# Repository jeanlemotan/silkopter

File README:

#########################################################################
#                                                                       #
#                                                                       #
#                                                                       #
#    _____ _ _ _           _                                            #
#   |   __|_| | |_ ___ ___| |_ ___ ___                                  #
#   |__   | | | '_| . | . |  _| -_|  _|                                 #
#   |_____|_|_|_,_|___|  _|_| |___|_|                                   #
#                     |_|                                               #
#                                                                       #
#                                                                       #
#  Copyright (C) 2014 Catalin Vasile                                    #
#                                                                       #
#  Web:     http://jeanleflambeur.wordpress.com/                        #
#  e-mail:  catalin.vasile@gmail.com                                    #
#                                                                       #
#                                                                       #
#########################################################################

This contains the code for the Silkopter UAV controller, ground station, simulator and additional libraries.

Folders:

qbase - base library with various utilities
qdata - filesystem and stream library
qinput - gamepad, mouse, touch and keyboard abstraction
qmath - math lib
q - 3d rendering engine used by the simulator and ground station
silkopter/fc - flight controller
silkopter/gs - ground station
silkopter/rc - remote control
silkopter/libs - common code used by the brain, gs and sim projects
printing/gimbal - a raspberry pi camera 2 axis gimbal
electrical/fc - eagle schematic and board layout for the silkopter fc

The q* libraries started initially as a mobile 3d game engine so most of the code is very game-oriented.

There are QTCreator projects in each folder and the whole code heavily uses C++11. It should compile with GCC4.7+ and clang3.2+

For licensing, check the LICENSE.txt file.

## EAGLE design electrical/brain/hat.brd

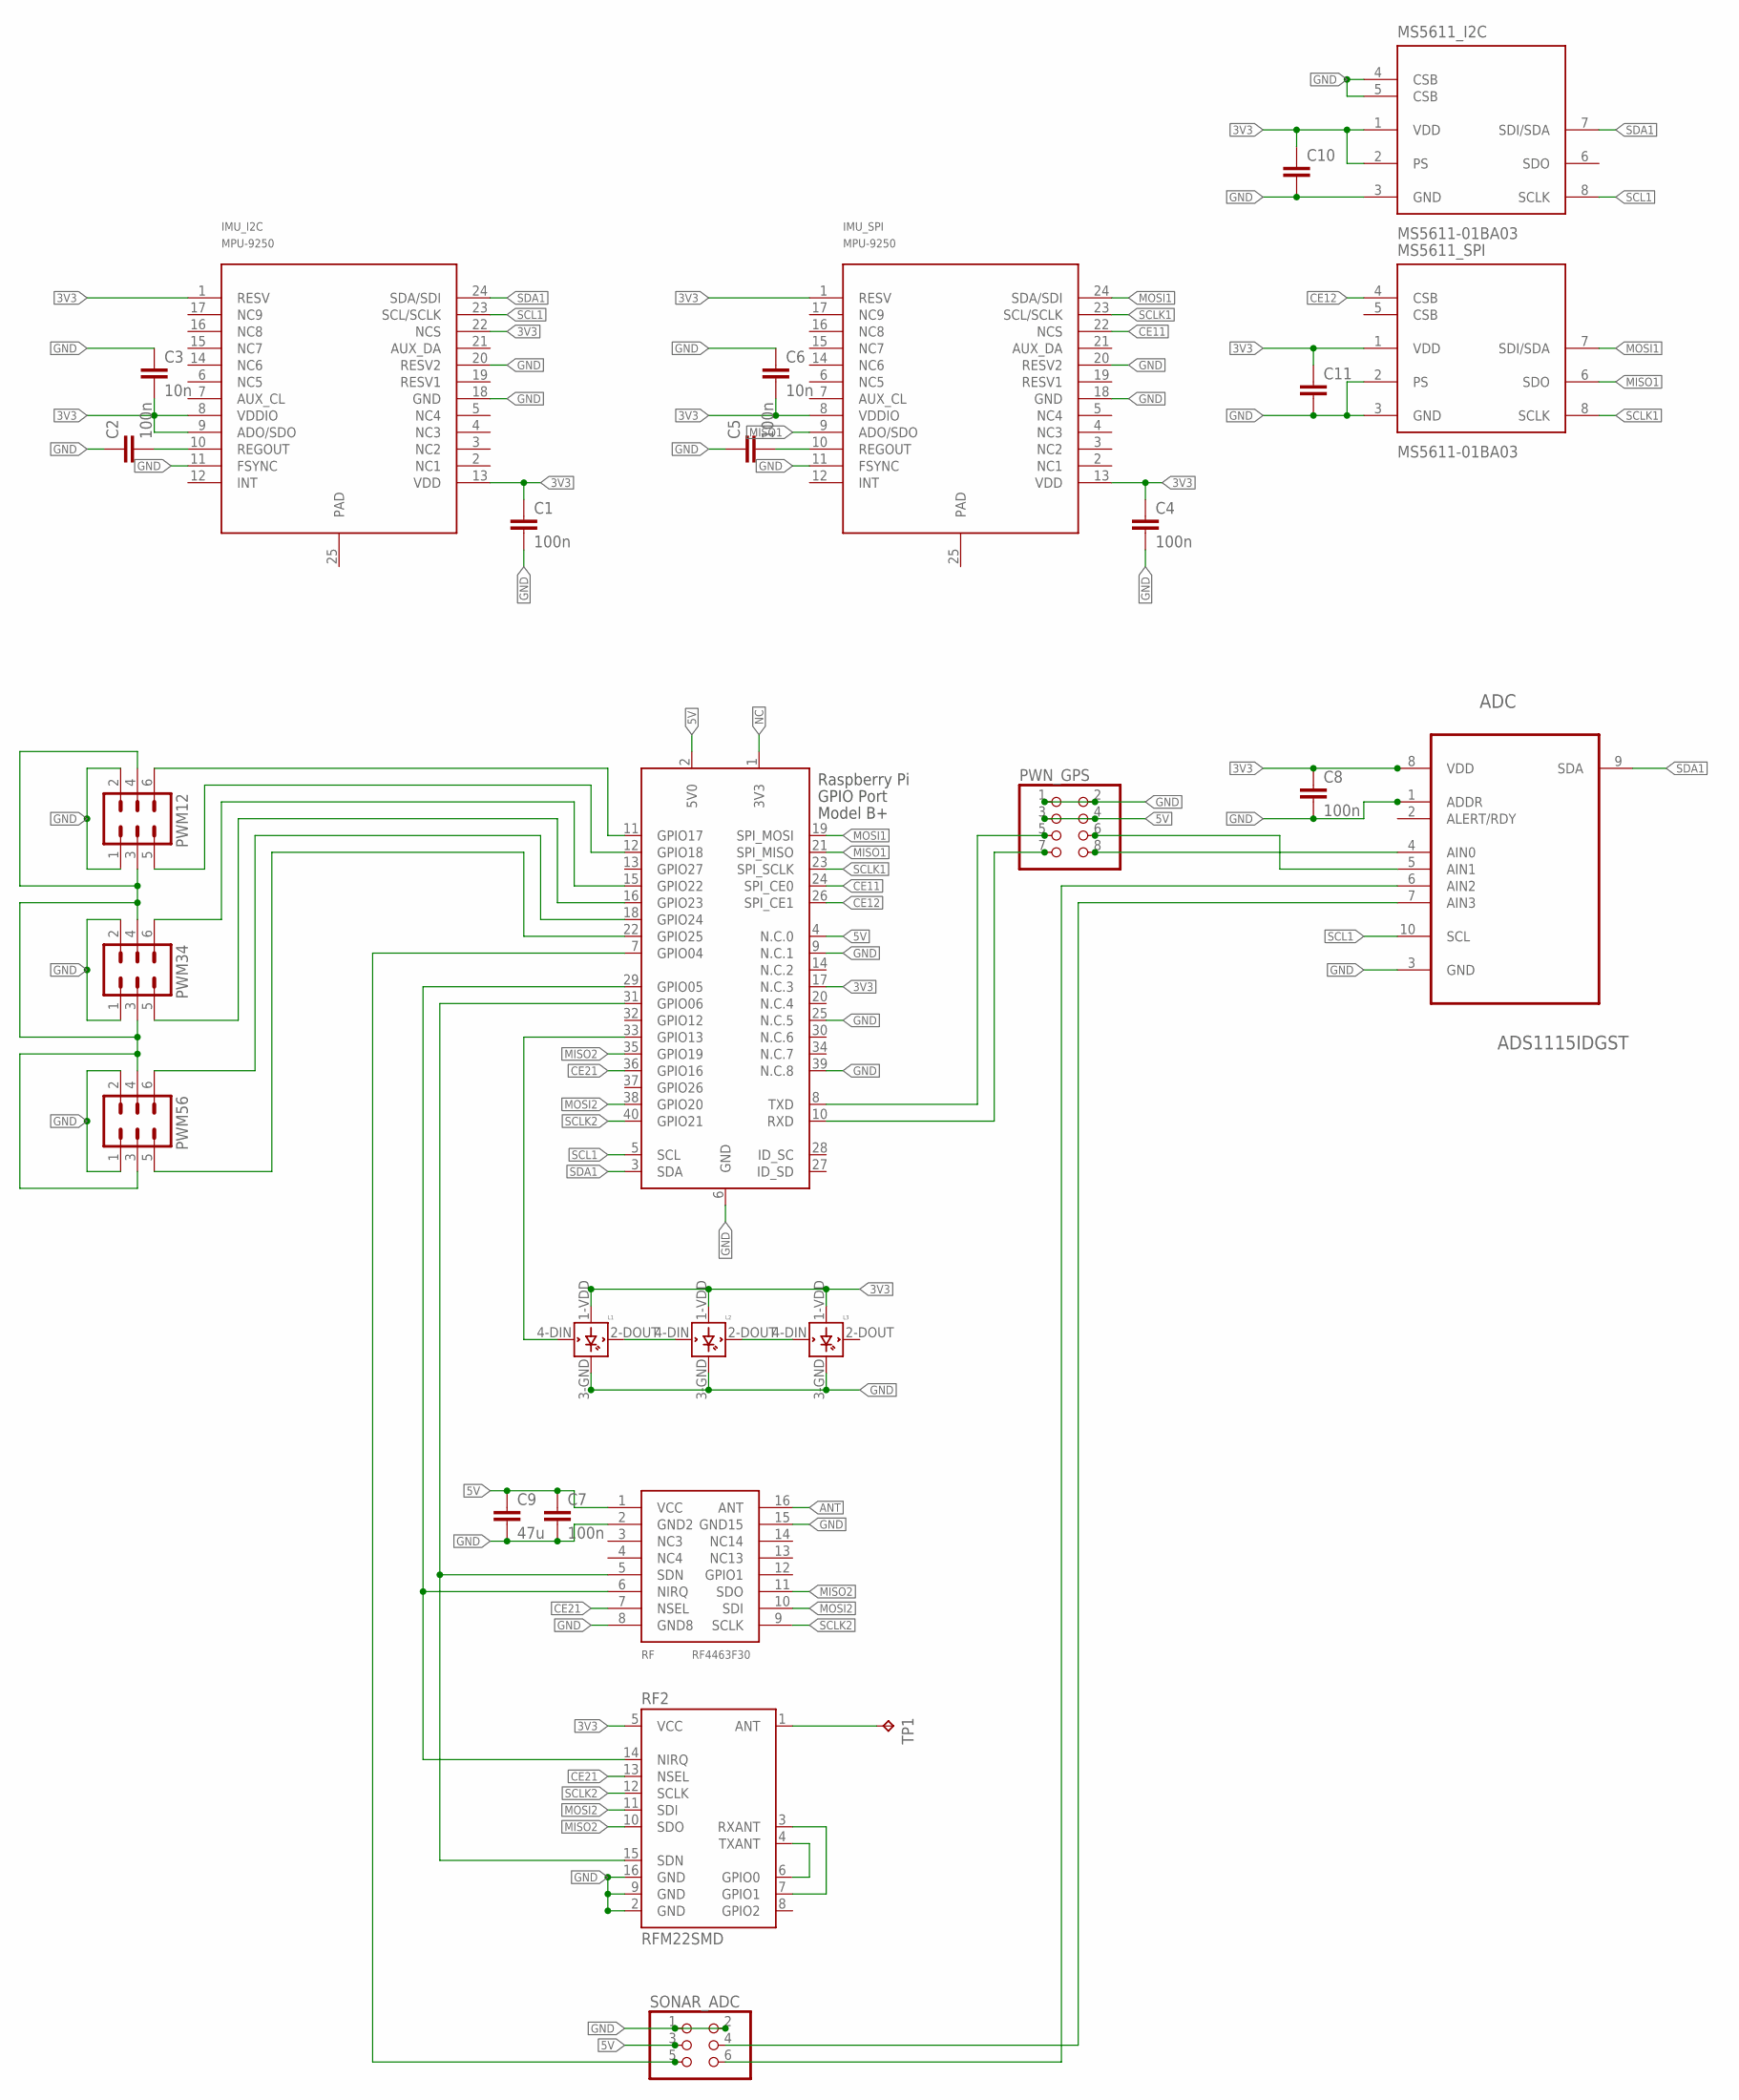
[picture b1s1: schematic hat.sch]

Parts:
ADC: ADS1115IDGST; SOP50P490X110-10N
C1, C2, C4, C5, C7, C8: 100n; C0603
C3, C6: 10n; C0603
C9: 47u; C0603
C10, C11: C-EUC0603; C0603
IMU_I2C: MPU-9250; LEAD-QFN24
IMU_SPI: MPU-9250; LEAD-QFN24
L1, L2, L3: WS2812B
MS5611_I2C, MS5611_SPI: MS5611-01BA03; SON125P300X500X100-8N
PWM12, PWM34, PWM56: MA03-2
PWN_GPS: PINHD-2X4/90; 2X04/90
RF: RF4463F30
RF2: RFM22SMD; RFM22-XXX-S2
SONAR_ADC: PINHD-2X3/90; 2X03/90
TP1: TPTP20SQ; TP20SQ
X1: RASPI_BOARD_B+_H; RASPI_BOARD_B+HAT

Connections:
3V3: ADC.8 (VDD), C1.1, C3.2, C4.1, C6.2, C8.1, C10.1, C11.1, IMU_I2C.1 (RESV), IMU_I2C.8 (VDDIO), IMU_I2C.9 (ADO/SDO), IMU_I2C.13 (VDD), IMU_I2C.22 (NCS), IMU_SPI.1 (RESV), IMU_SPI.8 (VDDIO), IMU_SPI.13 (VDD), L1.1-VDD (VDD), L2.1-VDD (VDD), L3.1-VDD (VDD), MS5611_I2C.1 (VDD), MS5611_I2C.2 (PS), MS5611_SPI.1 (VDD), RF2.5 (VCC), X1.17 (N.C.3)
5V: C7.1, C9.1, PWN_GPS.3, PWN_GPS.4, RF.1 (VCC), SONAR_ADC.3, X1.2 (5V0), X1.4 (N.C.0)
ANT: RF.16 (ANT)
CE11: IMU_SPI.22 (NCS), X1.24 (SPI_CE0)
CE12: MS5611_SPI.4 (CSB), X1.26 (SPI_CE1)
CE21: RF.7 (NSEL), RF2.13 (NSEL), X1.36 (GPIO16)
GND: ADC.1 (ADDR), ADC.3 (GND), C1.2, C2.1, C3.1, C4.2, C5.1, C6.1, C7.2, C8.2, C9.2, C10.2, C11.2, IMU_I2C.11 (FSYNC), IMU_I2C.18 (GND), IMU_I2C.20 (RESV2), IMU_SPI.11 (FSYNC), IMU_SPI.18 (GND), IMU_SPI.20 (RESV2), L1.3-GND (GND), L2.3-GND (GND), L3.3-GND (GND), MS5611_I2C.3 (GND), MS5611_I2C.4 (CSB), MS5611_I2C.5 (CSB), MS5611_SPI.2 (PS), MS5611_SPI.3 (GND), PWM12.1, PWM12.2, PWM34.1, PWM34.2, PWM56.1, PWM56.2, PWN_GPS.1, PWN_GPS.2, RF.2 (GND2), RF.8 (GND8), RF.15 (GND15), RF2.2 (GND), RF2.9 (GND), RF2.16 (GND), SONAR_ADC.1, SONAR_ADC.2, X1.6 (GND), X1.9 (N.C.1), X1.25 (N.C.5), X1.39 (N.C.8)
MISO1: IMU_SPI.9 (ADO/SDO), MS5611_SPI.6 (SDO), X1.21 (SPI_MISO)
MISO2: RF.11 (SDO), RF2.10 (SDO), X1.35 (GPIO19)
MOSI1: IMU_SPI.24 (SDA/SDI), MS5611_SPI.7 (SDI/SDA), X1.19 (SPI_MOSI)
MOSI2: RF.10 (SDI), RF2.11 (SDI), X1.38 (GPIO20)
unnamed: C2.2, IMU_I2C.10 (REGOUT)
unnamed: C5.2, IMU_SPI.10 (REGOUT)
unnamed: L1.2-DOUT (DOUT), L2.4-DIN (DIN)
unnamed: L2.2-DOUT (DOUT), L3.4-DIN (DIN)
unnamed: SONAR_ADC.5, X1.7 (GPIO04)
unnamed: ADC.6 (AIN2), SONAR_ADC.6
unnamed: ADC.7 (AIN3), SONAR_ADC.4
unnamed: PWM12.6, X1.11 (GPIO17)
unnamed: PWM12.5, X1.12 (GPIO18)
unnamed: L1.4-DIN (DIN), X1.33 (GPIO13)
unnamed: RF.5 (SDN), RF2.15 (SDN), X1.31 (GPIO06)
unnamed: ADC.5 (AIN1), PWN_GPS.6
unnamed: PWM34.6, X1.15 (GPIO22)
unnamed: PWM34.5, X1.16 (GPIO23)
unnamed: PWM56.6, X1.18 (GPIO24)
unnamed: PWM56.5, X1.22 (GPIO25)
unnamed: RF.6 (NIRQ), RF2.14 (NIRQ), X1.29 (GPIO05)
unnamed: RF2.1 (ANT), TP1.TP
unnamed: RF2.4 (TXANT), RF2.6 (GPIO0)
unnamed: RF2.3 (RXANT), RF2.7 (GPIO1)
unnamed: ADC.4 (AIN0), PWN_GPS.8
unnamed: PWN_GPS.5, X1.8 (TXD)
unnamed: PWN_GPS.7, X1.10 (RXD)
unnamed: PWM12.3, PWM12.4, PWM34.3, PWM34.4, PWM56.3, PWM56.4
NC: X1.1 (3V3)
SCL1: ADC.10 (SCL), IMU_I2C.23 (SCL/SCLK), MS5611_I2C.8 (SCLK), X1.5 (SCL)
SCLK1: IMU_SPI.23 (SCL/SCLK), MS5611_SPI.8 (SCLK), X1.23 (SPI_SCLK)
SCLK2: RF.9 (SCLK), RF2.12 (SCLK), X1.40 (GPIO21)
SDA1: ADC.9 (SDA), IMU_I2C.24 (SDA/SDI), MS5611_I2C.7 (SDI/SDA), X1.3 (SDA)

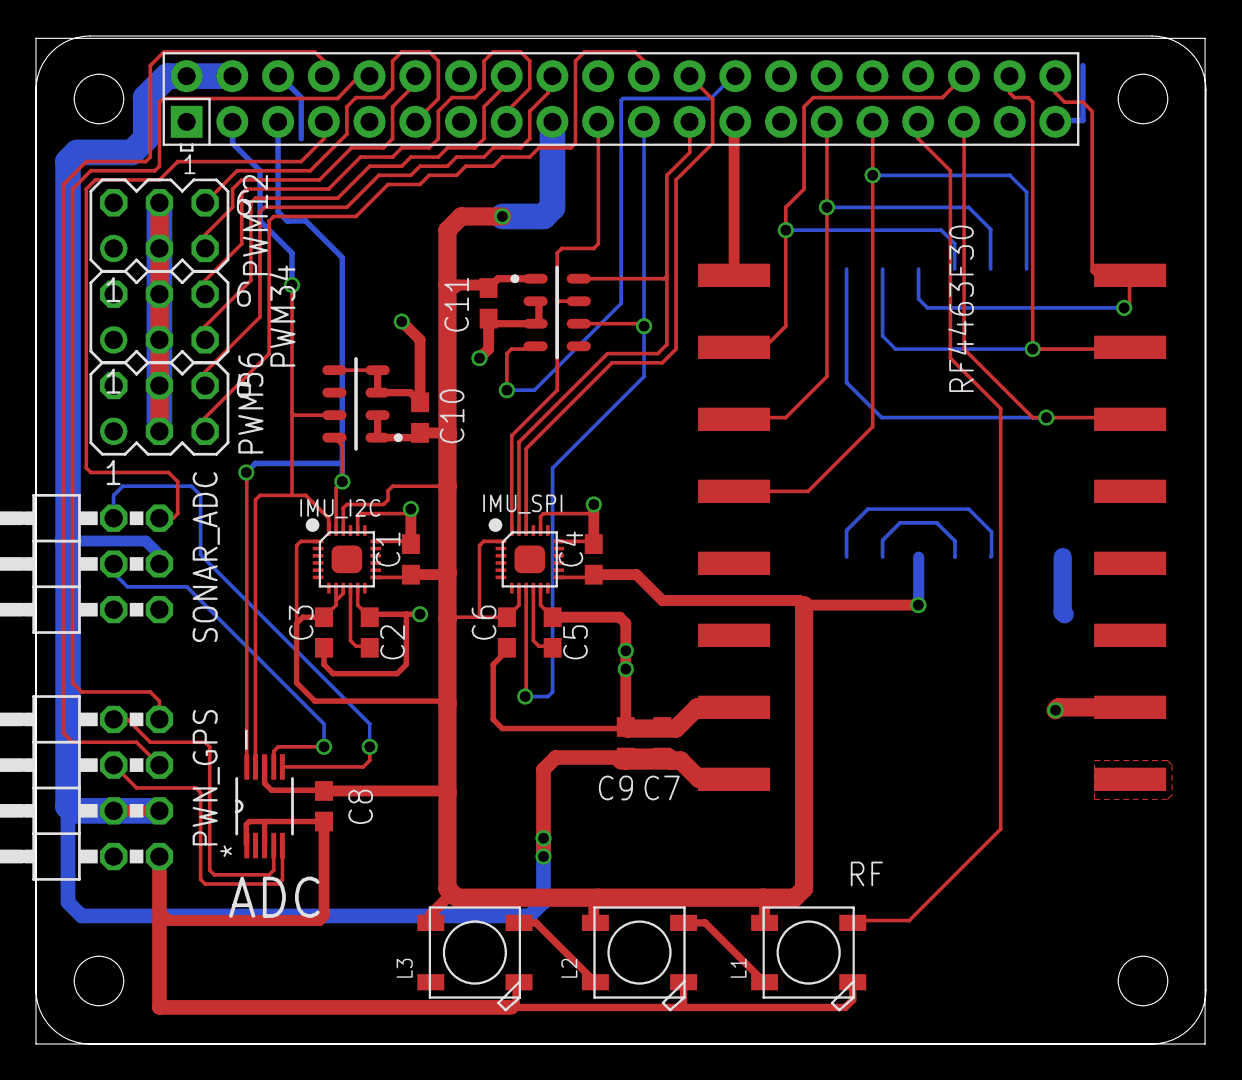
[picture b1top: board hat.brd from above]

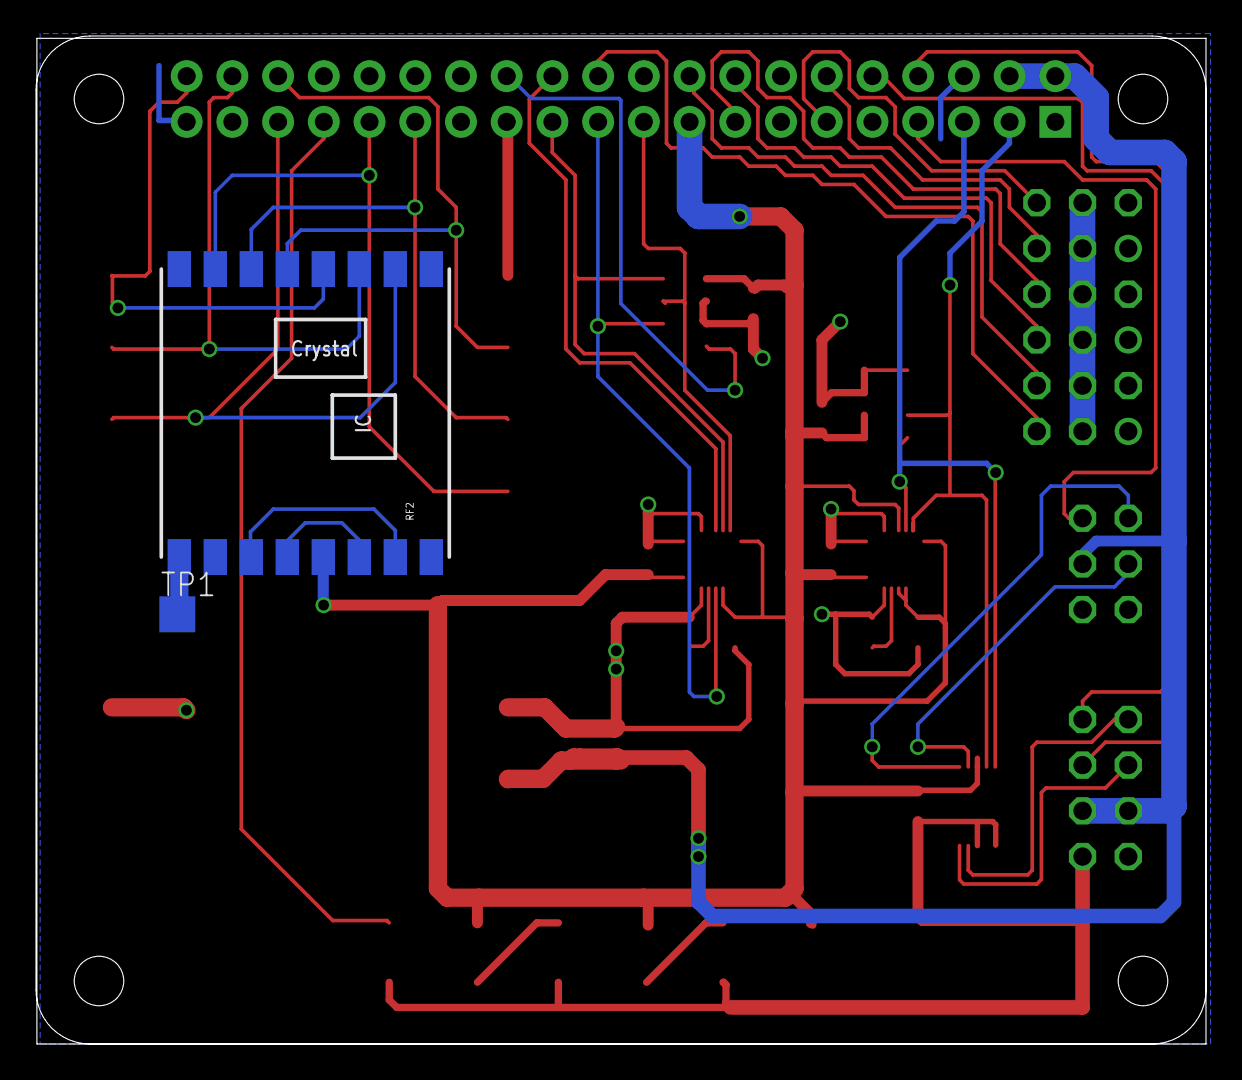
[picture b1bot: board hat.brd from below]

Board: 2 copper layers, 65.0 x 56.0 mm, 28 parts (2 on the bottom side), 38 nets.

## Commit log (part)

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2016-09-18 fixed crash
2016-09-18 poly value editing
2016-09-18 fixed the GC compilation
2016-09-19 Improved the attribute system Added ui_editor attribute Hex diting for i2c addresses
2016-09-20 Added internal telemetry viewer
2016-09-21 Fixed motor calculation
2016-10-10 Added switches and rotary encoders
2016-11-20 Added OLED screen support Started menu infrastructure Removed QT
2016-11-24 small fix
2016-11-24 consistency fix
2016-11-24 sleeping less for more responsiveness
2016-11-24 starting comms as well
2016-11-26 First test between brain and RC
2016-11-27 optimized a bit and removed leaks
2016-11-27 Fixed the double-fec datagrams when using more than 1 wifi card
2016-11-27 Fixed the interrupt handling
2016-11-27 added custom assert routine to allow continuing in debug
2016-11-27 added support for no-fft graphs
2016-11-27 Fix the video buffer growing indefinitely if not forwarding video
2016-11-28 Added settings
2016-11-29 First Settings
2016-12-08 compilation fix
2016-12-08 transmitting the actual commands instead of dummy data
2016-12-08 lowered power to reduce malfunctions during tx
2016-12-08 resettig the packet length when receiving
2016-12-08 lowered spi speed to hopefully fix the chip acting weird
2016-12-08 loading/saving settings and better initialization order
2016-12-10 RFM22B driver
2016-12-10 Added support for all spaces
2016-12-10 Sending the multi state
2016-12-10 Uncommented the idle state Computing the multi state correctly
2016-12-10 Storing ecef_position even though we're sending it in lla quantized
2016-12-10 Added RFM22B support
2016-12-10 Reboot support
2016-12-10 fixes
2017-01-01 propagating the comms to other pages
2017-01-01 fixed deserialization of commands using values instead of samples
2017-01-01 fixed crash in case of set node config failure
2017-01-01 compilation error
2017-01-01 sending comms to pages
2017-01-01 removed comms from input class
2017-01-01 added missing default value
2017-01-01 fixed acceleration calibration bug
2017-01-01 Removed useless libraries
2017-01-01 ignoring temp files
2017-01-06 Fixed config setting for the PIGPIO sink
2017-01-06 Added non-const getter for stick actuators
2017-01-06 More Fly menu page done
2017-01-06 Added mnissing font
2017-01-09 Removed the ARMED mode as it duplicated FLY
2017-01-09 Disabling and enabling the actuator if there is a target
2017-01-09 Added proper mode switches and processing for all modes
2017-01-11 fixed compilation issue
2017-01-11 Replaced lambdas with std::binds
2017-01-11 Blinking when changing modes Throttle stick feedback
2017-01-12 Simplified the ASIO channel
2017-01-12 Added Remove Viewer and Server to handle phone connectivity
2017-01-12 Comms info
2017-01-12 Remote viewer clean up Moved the Remte Viewr in the Comms
2017-01-13 Made everythng private
2017-01-13 Fixed some typos
2017-01-21 New files
2017-01-21 Working on the device
2017-01-22 Fixed some includes
2017-01-22 Fullscreen mode Faster decoding
2017-01-22 Added menu structure, icons and qml proxies
2017-01-22 Moved the the silkopter folder
2017-01-22 Lowered the comms rate to allow for incoming meessages at low bitrate
2017-01-22 Mostly comms fixes and optimizations
2017-01-22 Reduced rate to avoid rx timeouts at low bitrates
2017-01-22 Added customizable assert macro
2017-01-22 avoiding polluting global namespace
2017-01-23 Fixed compilation
2017-01-23 Fixed the locale
2017-01-24 Revamped the brain a bit
2017-01-24 Reorganized the Brain config params More work on the brain input and flight modes
2017-01-25 Reorganized the navigation code Return home should work now
2017-01-25 Removed the position command, as it's redundant with velocity
2017-01-27 Removed qdata dependency Cleaned up some includes and code
2017-01-27 Removed qdata Fixed compilation issues
2017-01-27 Removed unused include
2017-01-27 Streaming and UI working
2017-01-28 Revived messages Added back the simulator node Linking with libbullet
2017-01-28 Replaced the high_resolution_clock with the steady_clock
2017-01-29 Started the simulator renderer using Qt3D this time
2017-01-29 Aded messages def and moved all messages there
2017-01-31 allowing initialization from initializer_list
2017-01-31 Fixed the missing name in the message
2017-01-31 Properly initializing values
2017-02-01 Allow disabling RTH
2017-02-01 Commented out verbose log
2017-02-02 Back to bullet due to performance and instability
2017-02-02 Renamed the rate pid to angle pid Fixed the stick ranges
2017-02-02 fixed warning
2017-02-02 Fixed reset and stop actions
2017-02-05 Sending the simulator state as telemetry instead of messages Max 200HZ physics simulation due to bullet issues at 1000Hz
2017-02-05 Renamed rate pid to angle pid
2017-02-05 Showing internal telemetry as percentage
2017-02-05 Fixed compilation issue on the pi due to lack of boost C++11 support
2017-02-05 catching asserts
2017-02-05 small fixes
2017-02-06 Better flight modes
2017-02-07 Commented out some code Renamed the VELOCITY horizontal mode to POSITION
2017-02-10 Computing the average thrust so that when changing from ALT-HOLD to normal vertical mode, the quad maintains altitude Allowing yaw control in RTH mode if the input is healthy
2017-02-10 Added health info for all the streams
2017-02-11 ECEF and ENU viewers
2017-02-11 Fixed ECEF position de/serialization
2017-02-11 Various small cleanups
2017-02-11 Added some altitude in the fake data
2017-02-11 Removed verbose log
2017-02-12 Removed the interned string Working in the GS
2017-02-12 Redefines Clock and default duration
2017-02-12 Added a delay to let the voltage stabilize
2017-02-12 Sending min/max limits to the PID to fix integral wind-up
2017-02-12 Hardened against pipeline stalling
2017-02-12 Sending the Multirotot State as part of the simulation state
2017-02-12 Replaced Qt 3D with Q for better performance and other fixes
2017-02-12 Fixed altitude / 10 bug
2017-02-12 Fixed crash due to opengl context being changed by QT Optimized a bit the graph rendering
2017-02-12 Resetting the yaw angle target to the current yaw in idle mode
2017-02-12 Showing --- for vh modes in RTH
2017-02-12 Fixed mode handling and transitions
2017-02-13 Added RC session to reset the packet indices when one party connects When connecting, the RC asks for vital data (like home)
2017-02-19 Started working on params, to replace the descriptor/config system
2017-02-19 tried a different way of non-blocking serial
2017-02-19 Cosmetic fixes
2017-02-19 Started the rename to FC
2017-02-19 added back the source as the shitty rename failed
2017-02-19 Removed unneded ignores Renamed from Brain to FC
2017-02-19 Collapsed all ignores into one
2017-02-19 Renamed Brain to FC
2017-03-25 renamed from brain to fc
2017-03-25 updated info
2017-04-02 Fixed the angles
2017-04-04 Added support for inverted text using \1
2017-04-04 Battery info and calibration menus
2017-04-08 Added a motor mixer specific for quads
2017-04-08 Fixed a silly contention bug that was causing huge (30+ms) delays when sampling the IMU
2017-04-08 Quad motor mixer
2017-04-25 Added boost headers
2017-04-25 Kill the app when put to background
2017-04-25 Increased the min device
2017-04-25 Ignoring build temp files
2017-04-25 Sending more data to the viewer
2017-05-01 Fixed the video glitch Started telemetry code
2017-05-01 Added video data rate in the info screen
2017-05-02 Made the viewer work (kind of) on desktop
2017-05-02 Fixed serialization bug
2017-05-02 Auto connecting when starting up
2017-05-02 Adding qbase and qmath dependencies
2017-05-03 fixed qml warning
2017-05-03 Added battery bar + map
2017-05-06 Including the auto buffer directly
2017-05-06 Various connection fixes - like auto retries and auto connect
2017-05-06 Using QLOG instead of raw androud logging
2017-05-06 Path history
2017-05-06 upgraded to qt 5.9
2017-05-06 Telemetry is out of the comms now for QML
2017-05-07 60FPS to save battery
2017-05-07 black icons
2017-05-07 icons
2017-05-07 missing include
2017-05-07 sendind the resolution
2017-05-07 removed too verbose logs
2017-05-07 Added camera commands Creating the recording file sink on the recording thread to avoid freezes on the main thread
2017-05-07 camera commands stream
2017-05-07 removed verbose logs
2017-05-08 Ability to change the carrier frequency and xtal compensation cap
2017-05-08 rf settings
2017-05-13 Fixed viewo stats
2017-05-13 Rate PID params are scaled up by 100 now
2017-05-20 remoed qmapcontrol as it's not used anymore
2017-05-28 Removed unused io_board
2017-06-01 Better deserialization code
2017-06-01 fixed deserialization
2017-06-01 Setting the SPI device from outside of the hw chip
2017-06-01 Added chained transfer support
2017-06-01 Lots of throughput and general fixes
2017-06-01 latest pigpio version
2017-06-01 Creating the SPI device from outside of the hw chip
2017-06-01 added pigpio spi device in the project
2017-06-02 new config
2017-06-02 Working with 10 mhz
2017-06-02 Finally stable comms Also, 2 byte length, so big packets
2017-06-03 Added test application for the RC protocol
2017-06-03 Templated consumer-producer queue
2017-06-03 Added reliable, periodic and fec packet support Added CRC support
2017-06-03 Added separate RX packet and payload timeouts Improved the FRR reading
2017-06-03 FEC working Throughput: ~67-68Kbps FEC bandwidth increase (for 5/7 coding): ~30-40%
2017-06-04 added clearing
2017-06-04 fixed block index wrapping
2017-06-04 Added explicit timeout for TX
2017-06-04 Added exploicit TX timeout
2017-06-05 removed the nirq gpio as it wasn't used
2017-06-05 Changes for the latest RC_Protocol
2017-06-05 Increasd the signal bar range for the si4463 improved sensitivity
2017-06-05 Commented out for now
2017-06-05 Fixed nasty deadlock after clearing
2017-06-05 Removed the INTRA-FRAME refresh as it was increasing the bandwidth
2017-06-05 Added dBm for video link
2017-06-07 Added reset when the chip stops responding
2017-06-11 Reverted back to the RFM22B
2017-06-11 Compilation warning
2017-06-11 Reduced the SPI speed in an attempt to reduce the si4463 timeouts
2017-06-17 Renamed dsp to lfp in some places Added some randomness to the motor thrust value
2017-06-18 Moving the main thread to the reserved core
2017-06-18 Android viewer works through USB tethering now
2017-08-28 added stand-alone asio
2017-08-29 Added bullet
2017-08-30 small fix to avoid a 20 seconds deadlock (thread starving whe ncalling set_channel)
2017-09-03 Using stand-alone asio instead of boost::asio
2017-09-03 Handled properly a corrupt-packet error that was causing the RC to crash
2017-09-03 Added a mutex for viewer connect/disconnect
2017-09-06 Showing frames as euler angles
2017-09-06 Fixed crash when probing for the remote viewer
2017-09-06 Added panic disarm button
2017-09-07 Fixed yaw mixing bug
2017-09-07 Fixed rate validation bug
2017-09-07 Added stick curve (exp controls)
2017-09-10 Removed the android viewer
2017-09-10 Fixed crash due to missing mutex lock
2017-09-10 Added iframe interval setting
2017-09-10 Back to QT UI and touchscreen
2017-09-10 Started QML hud code
2017-09-11 Fixed missing include
2017-09-11 Added HUD
2017-09-11 Added icons/images for the hud
2017-09-11 Images/icons for the hud
2017-09-26 Fec + Queue + Pool from my esp github
2017-09-26 Using ESP for comms
2017-09-26 Fixed typo
2017-09-26 Using a proper queue for video buffering
2017-09-26 Mode switching UI
2017-09-26 Compiling on linux desktop for testing
2017-09-26 Battery indicator
2017-10-01 FEC and rate params per quality Recreating the fec when quality changes
2018-03-18 Added Ultimate Sensor Fusion sensor support
2018-07-19 Replaced esp8266 with esp32
2018-07-19 Removed QT and replaced it with imgui
2018-07-20 Video almost working
2018-07-20 Removed temp files
2018-07-22 Added multiple phy Added stats
2018-08-15 rc working
2018-09-05 Fixed RX bug when there are too many TX packets
2018-09-08 Error checking for failed phy
2018-09-08 Attempt to make i2c slightly faster in debug Fixed come compialtion errors
2018-09-08 Inverted the camera image
2018-09-08 Missing includes
2018-09-22 One thread per phy

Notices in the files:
parts and their libraries:
SparkFun: Licensing: CC v3.0 Share-Alike You are welcome to use this library for commercial purposes.
